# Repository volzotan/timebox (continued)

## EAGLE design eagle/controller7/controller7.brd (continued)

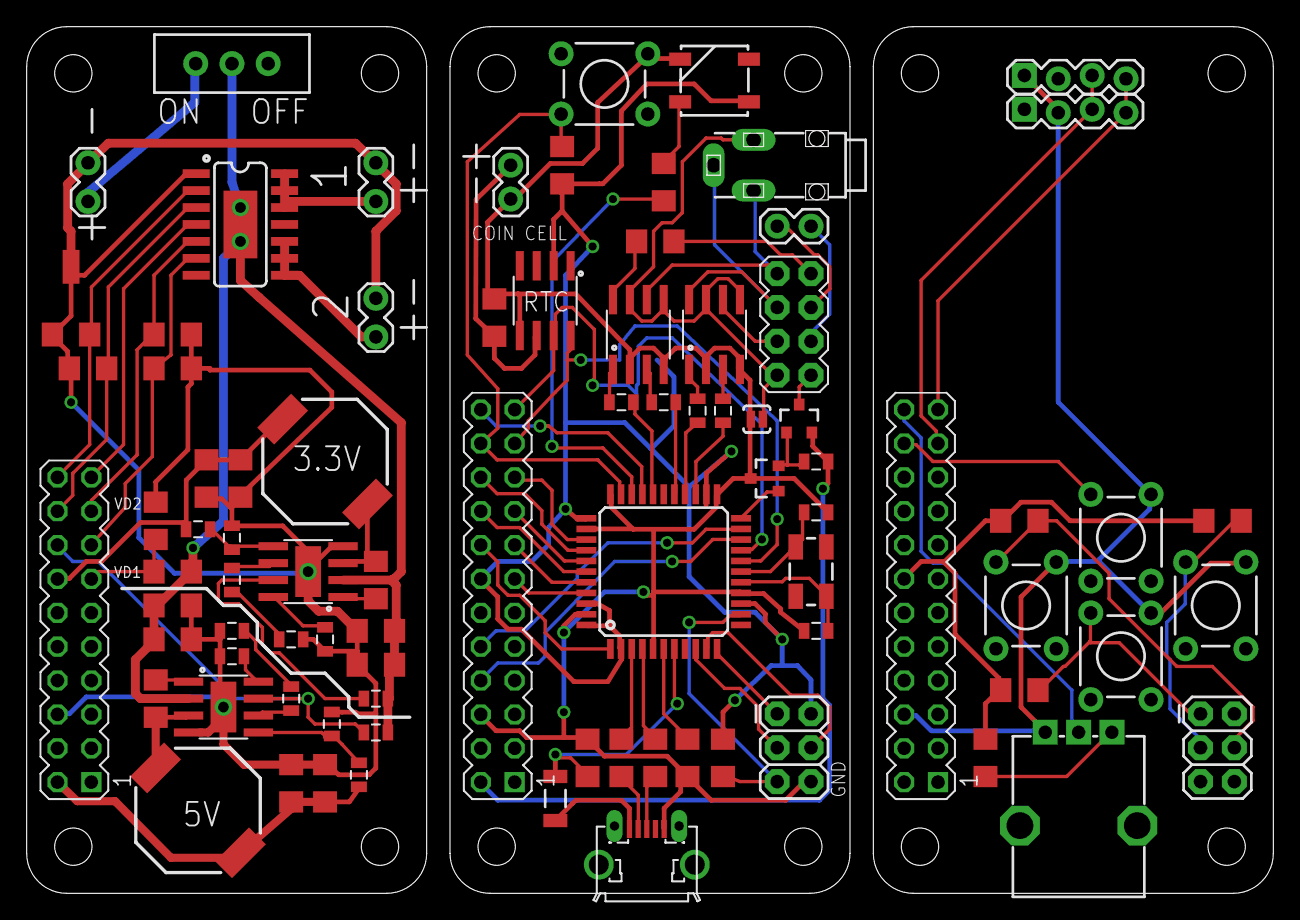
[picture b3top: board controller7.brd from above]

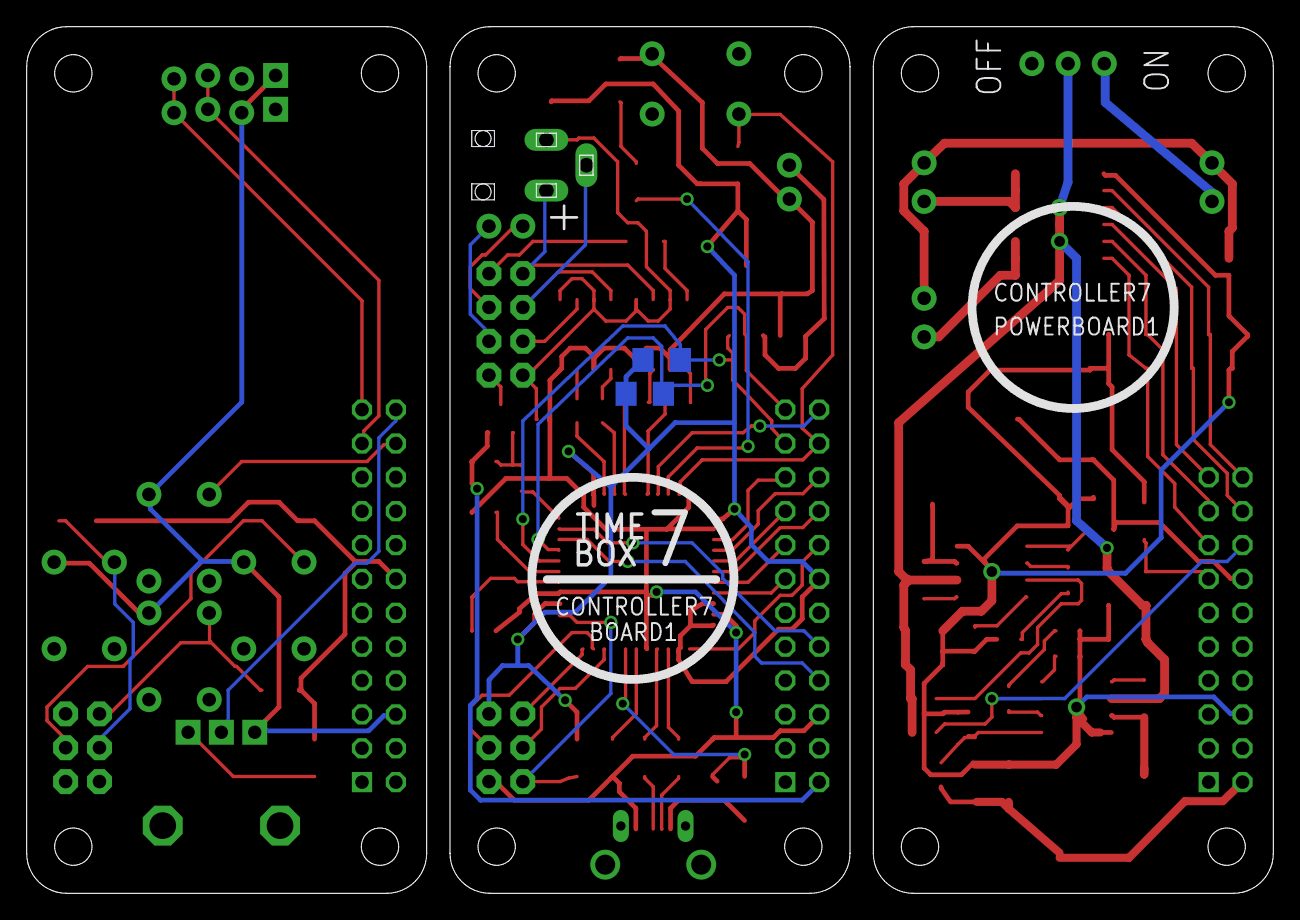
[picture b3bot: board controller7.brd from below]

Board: 2 copper layers, 93.5 x 65.0 mm, 88 parts (2 on the bottom side), 89 nets.

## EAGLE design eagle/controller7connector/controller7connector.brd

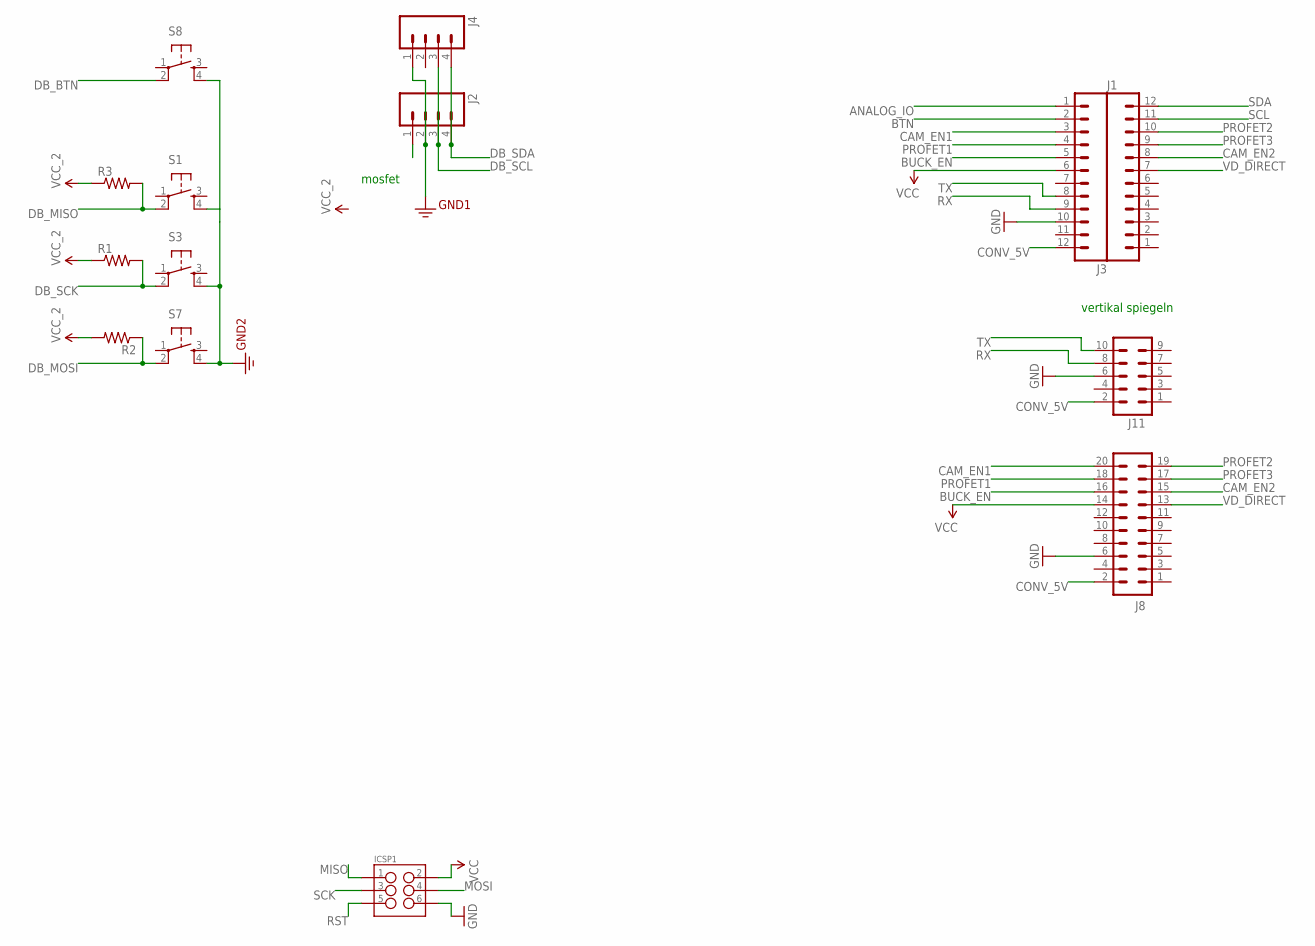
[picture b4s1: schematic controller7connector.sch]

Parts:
ICSP1: M03X2FEMALE; 2X3
J1, J3: M12PTH; 1X12
J2, J4: M04LOCK; 1X04_LOCK
J8: M10X2; 2X10
J11: M05X2NO_SILK; 2X5_NOSILK
R1, R2, R3: RESISTOR1206; 1206
S1, S3, S7, S8: TAC_SWITCHPTH; TACTILE-PTH

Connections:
3.3V: J2.2, J4.1, S1.4, S3.4, S7.4, S8.4
ANALOG_IO: J3.1
BTN: J3.2
BUCK_EN: J3.5, J8.16
CAM_EN1: J3.3, J8.20
CAM_EN2: J1.8, J8.15
CONV_5V: J3.12, J8.2, J11.2
DB_BTN: S8.2
DB_MISO: R3.2, S1.2
DB_MOSI: R2.1, S7.2
DB_SCK: R1.2, S3.2
DB_SCL: J2.3, J4.3
DB_SDA: J2.4, J4.4
GND: ICSP1.6, J3.10, J8.6, J11.6
MISO: ICSP1.1
MOSI: ICSP1.4
PROFET1: J3.4, J8.18
PROFET2: J1.10, J8.19
PROFET3: J1.9, J8.17
RST: ICSP1.5
RX: J3.9, J11.8
SCK: ICSP1.3
SCL: J1.11
SDA: J1.12
TX: J3.8, J11.10
VCC: ICSP1.2, J3.6, J8.14
VCC_2: R1.1, R2.2, R3.1
VD_DIRECT: J1.7, J8.13

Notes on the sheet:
mosfet
vertikal spiegeln

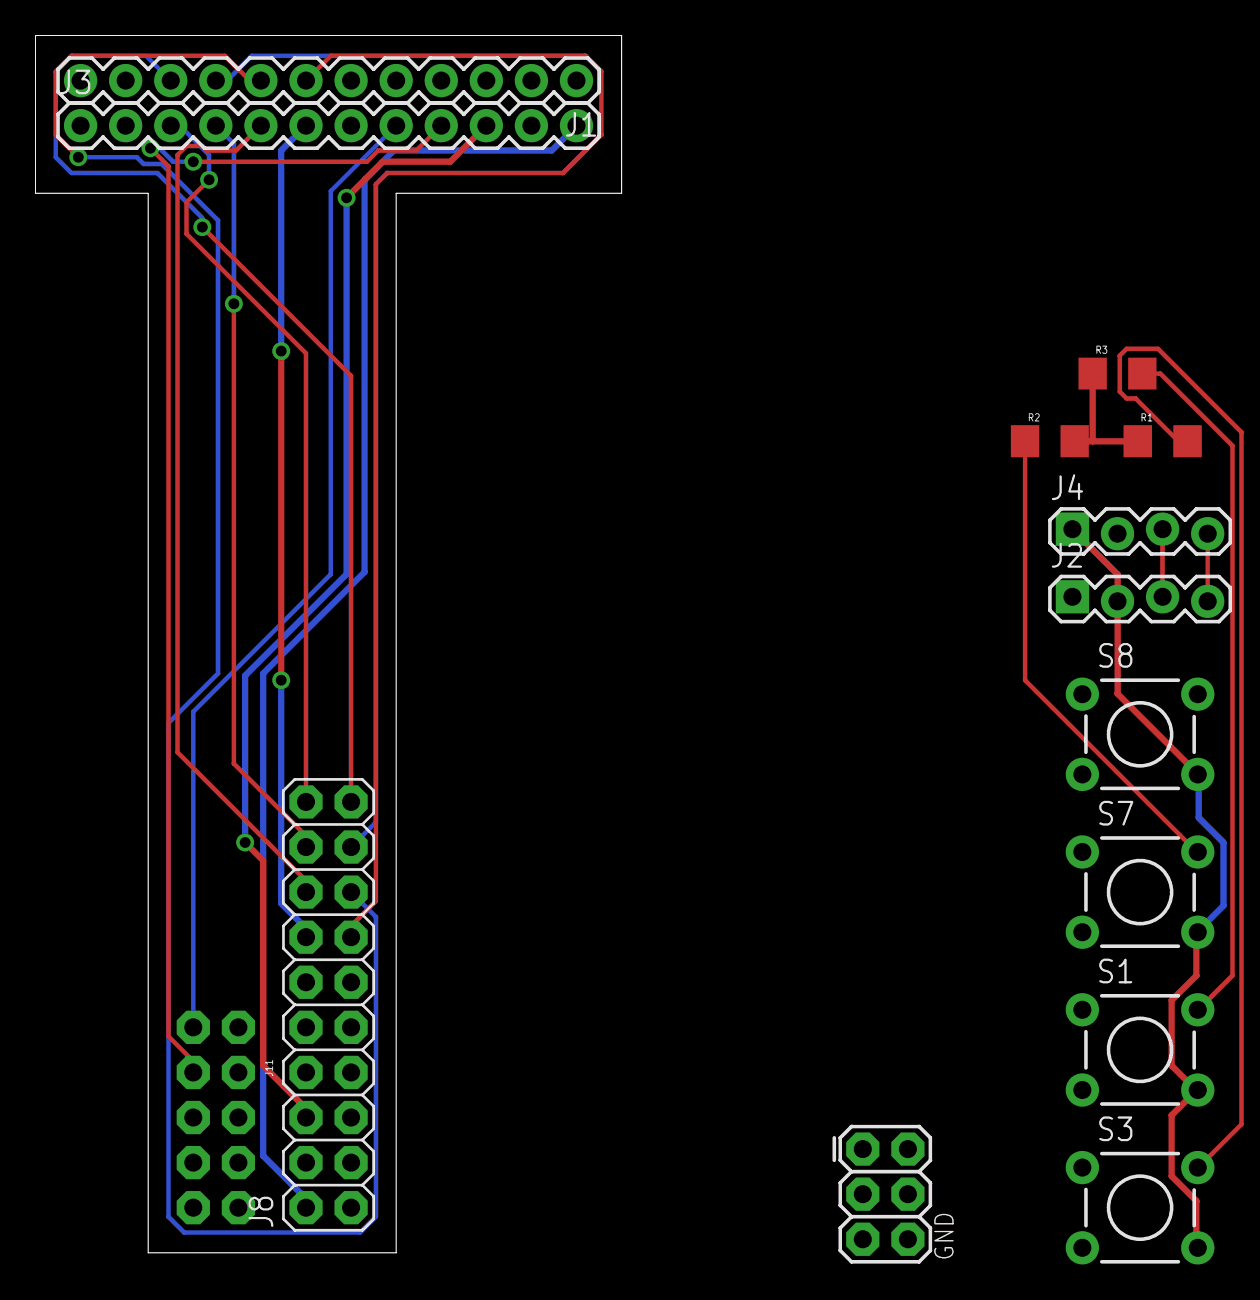
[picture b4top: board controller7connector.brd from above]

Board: 2 copper layers, 33.0 x 68.6 mm, 14 parts (0 on the bottom side), 19 nets.

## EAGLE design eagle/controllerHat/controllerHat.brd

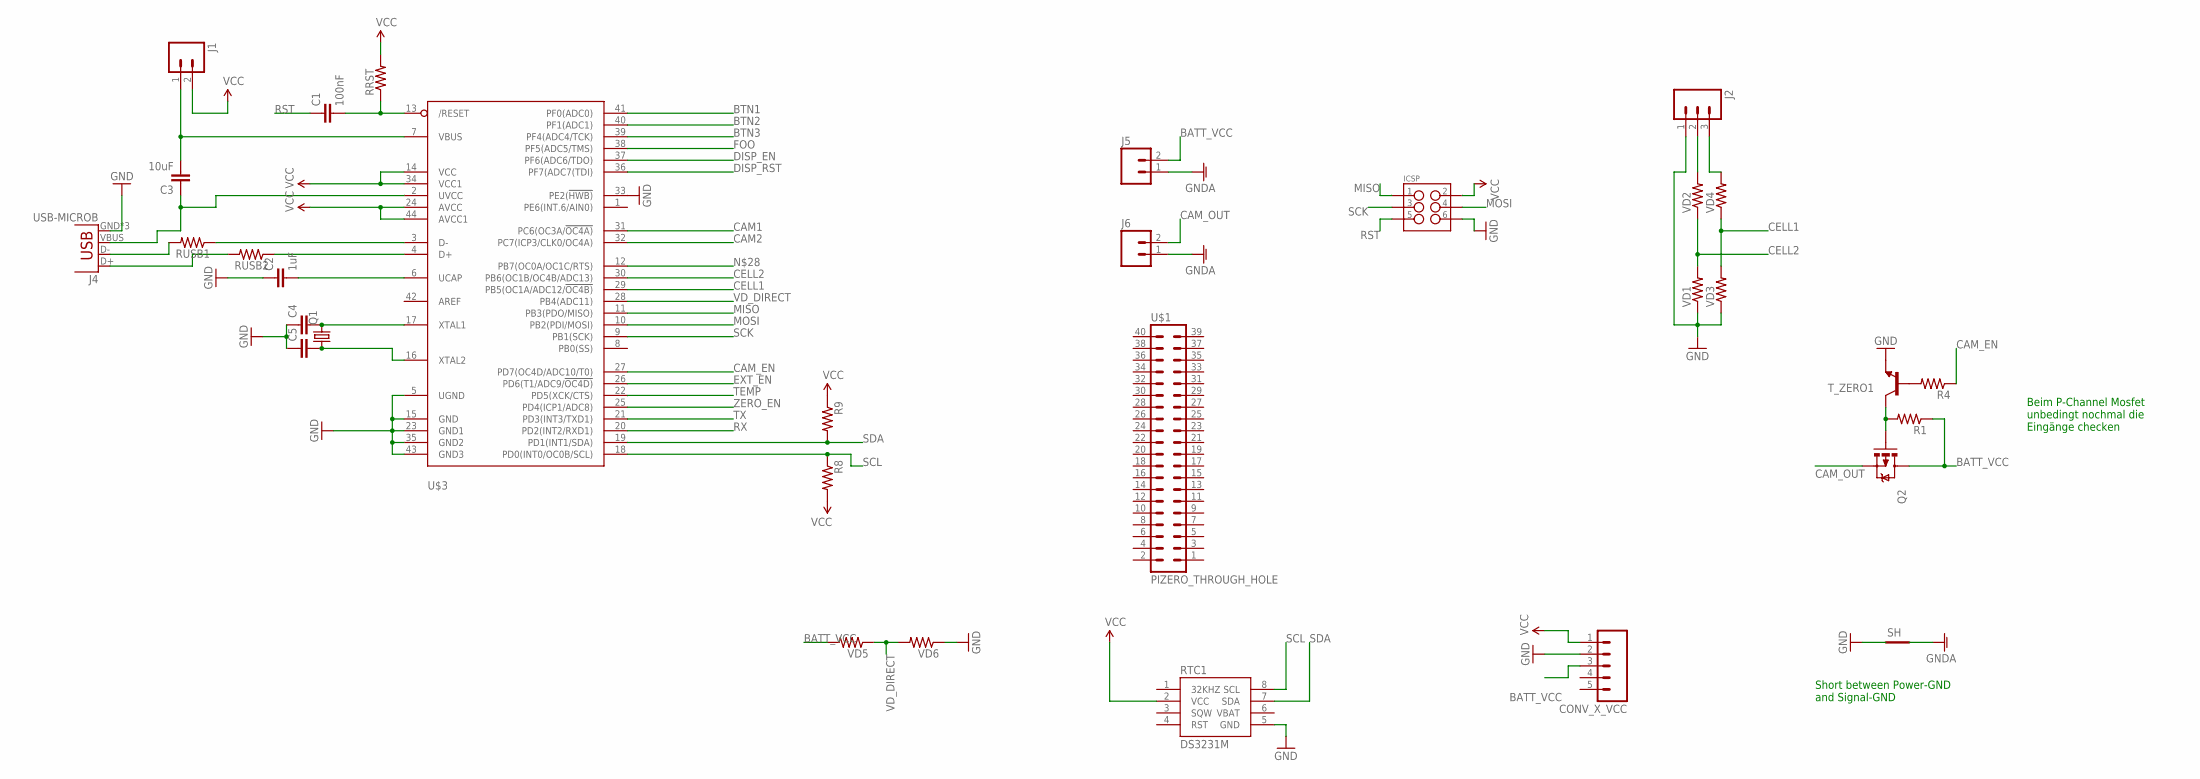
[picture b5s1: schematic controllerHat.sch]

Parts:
C1: 100nF; 1206
C2: 1uF; 1206
C3: 10uF; 1206
C4, C5: CAP1206; 1206
CONV_X_VCC: M05LOCK; 1X05_LOCK
ICSP: M03X2FEMALE; 2X3
J1: M02LOCK; 1X02_LOCK
J2: M03LOCK; 1X03_LOCK
J4: USB-MICROB
J5, J6: M023.5MM_LOCK; SCREWTERMINAL-3.5MM-2_LOCK
Q1: CRYSTALMM20SS; MM20SS
Q2: MOSFET-PCHANNELNDP6020P_20V_24A_LOW_VGS_TH; TO220V
R1, R4, R8, R9: RESISTOR1206; 1206
RRST: RESISTOR1206; 1206
RTC1: DS3231M; SOIC8
RUSB1, RUSB2: RESISTOR1206; 1206
SH: SHORT-HT5; SHORT_TOP-50
T_ZERO1: TRANSISTOR_NPN2N3904; TO-92
U$1: PIZERO_THROUGH_HOLE; PIZERO_THOUGH_HOLE
U$3: ATMEGA32U4-AU; TQFP44
VD1, VD2, VD3, VD4, VD5, VD6: RESISTOR1206; 1206

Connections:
BATT_VCC: CONV_X_VCC.3, J5.2, Q2.2 (D), R1.1, VD5.2
BTN1: U$3.41 (PF0(ADC0))
BTN2: U$3.40 (PF1(ADC1))
BTN3: U$3.39 (PF4(ADC4/TCK))
CAM1: U$3.31 (PC6(OC3A/!OC4A))
CAM2: U$3.32 (PC7(ICP3/CLK0/OC4A))
CAM_EN: R4.1, U$3.27 (PD7(OC4D/ADC10/T0))
CAM_OUT: J6.2, Q2.3 (S)
CELL1: U$3.29 (PB5(OC1A/ADC12/!OC4B)), VD3.2, VD4.1
CELL2: U$3.30 (PB6(OC1B/OC4B/ADC13)), VD1.2, VD2.1
DISP_EN: U$3.37 (PF6(ADC6/TDO))
DISP_RST: U$3.36 (PF7(ADC7(TDI))
EXT_EN: U$3.26 (PD6(T1/ADC9/!OC4D))
FOO: U$3.38 (PF5(ADC5/TMS))
GND: C2.1, C4.1, C5.1, CONV_X_VCC.2, ICSP.6, J2.1, J4.GND, J4.MT1 (GND), J4.MT2 (GND), RTC1.5 (GND), SH.1, T_ZERO1.1 (E), U$3.5 (UGND), U$3.15 (GND), U$3.23 (GND1), U$3.33 (PE2(!HWB)), U$3.35 (GND2), U$3.43 (GND3), VD1.1, VD3.1, VD6.1
GNDA: J5.1, J6.1, SH.2
MISO: ICSP.1, U$3.11 (PB3(PDO/MISO))
MOSI: ICSP.4, U$3.10 (PB2(PDI/MOSI))
unnamed: C1.2, RRST.1, U$3.13 (/RESET)
unnamed: J2.3, VD4.2
unnamed: J2.2, VD2.2
unnamed: RUSB1.1, U$3.3 (D-)
unnamed: RUSB2.1, U$3.4 (D+)
unnamed: R4.2, T_ZERO1.2 (B)
unnamed: C4.2, Q1.4 (2), U$3.17 (XTAL1)
unnamed: C5.2, Q1.1, U$3.16 (XTAL2)
unnamed: C3.2, J1.1, U$3.7 (VBUS)
unnamed: J4.D-, RUSB1.2
unnamed: J4.D+, RUSB2.2
unnamed: C2.2, U$3.6 (UCAP)
unnamed: Q2.1 (G), R1.2, T_ZERO1.3 (C)
unnamed: C3.1, J4.VBUS, U$3.2 (UVCC)
RST: C1.1, ICSP.5
RX: U$3.20 (PD2(INT2/RXD1))
SCK: ICSP.3, U$3.9 (PB1(SCK))
SCL: R8.1, RTC1.8 (SCL), U$3.18 (PD0(INT0/OC0B/SCL))
SDA: R9.2, RTC1.7 (SDA), U$3.19 (PD1(INT1/SDA))
TEMP: U$3.22 (PD5(XCK/CTS))
TX: U$3.21 (PD3(INT3/TXD1))
VBAT: RTC1.6 (VBAT)
VCC: CONV_X_VCC.1, ICSP.2, J1.2, R8.2, R9.1, RRST.2, RTC1.2 (VCC), U$3.14 (VCC), U$3.24 (AVCC), U$3.34 (VCC1), U$3.44 (AVCC1)
VD_DIRECT: U$3.28 (PB4(ADC11)), VD5.1, VD6.2
ZERO_EN: U$3.25 (PD4(ICP1/ADC8))

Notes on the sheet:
Short between Power-GND and Signal-GND
Beim P-Channel Mosfet unbedingt nochmal die Eingänge checken

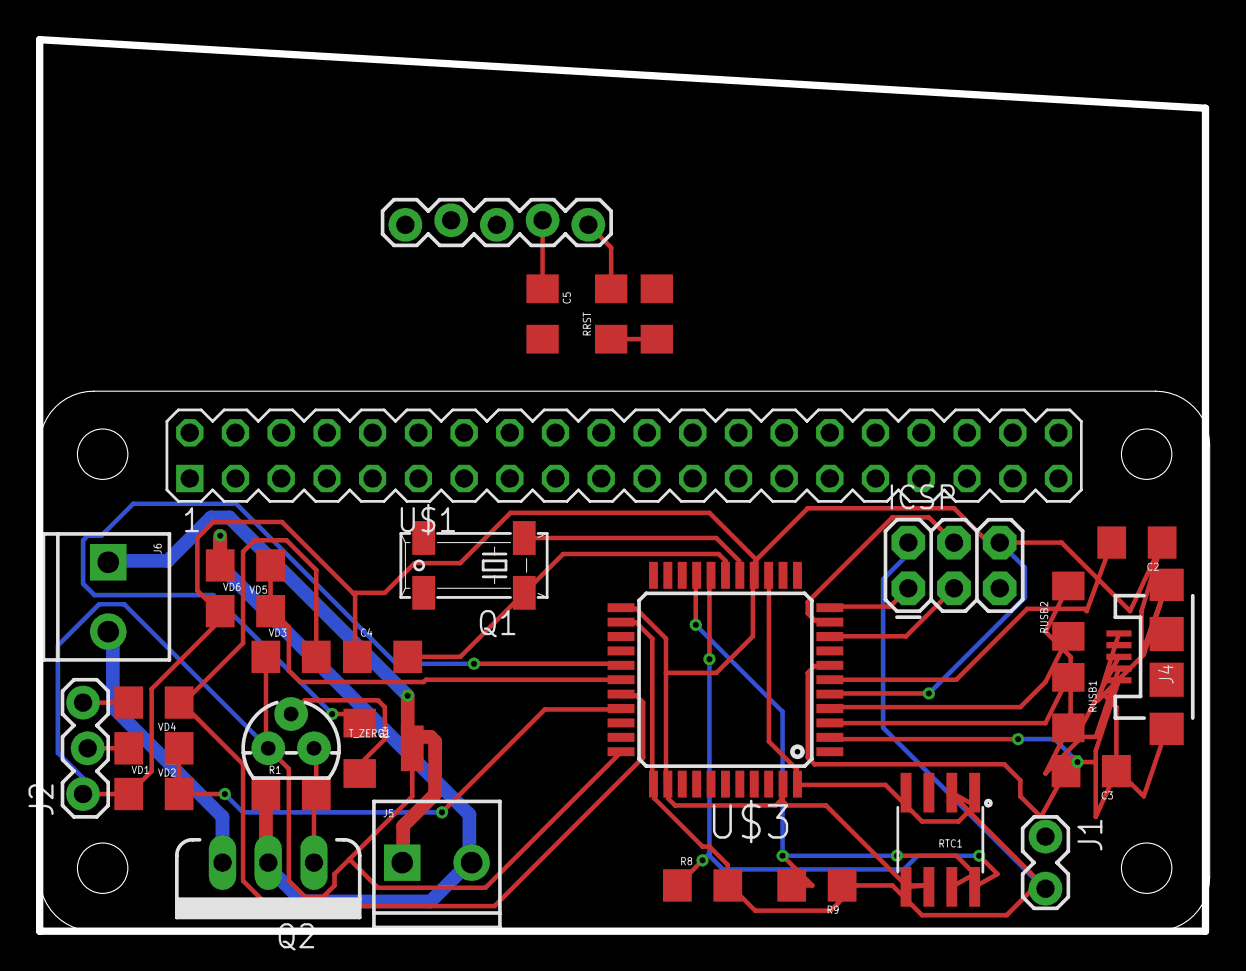
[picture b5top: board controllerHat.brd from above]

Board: 2 copper layers, 64.8 x 49.5 mm, 32 parts (0 on the bottom side), 29 nets.
